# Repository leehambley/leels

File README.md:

# leels: single-axis electronic gearbox

A Rust/Embassy port of the gearbox mode of
[NanoEls H5](https://github.com/kachurovskiy/nanoels), cut down to one job:
the Z lead screw follows the spindle at the selected pitch. There is no WiFi,
no other modes, no X/Y axis, no keyboard or joystick, and no GCode.

```
els-core/   hardware-independent logic, no_std, host-tested (cargo test)
firmware/   esp-hal + esp-rtos (Embassy) binary; ESP32-C6 primary, ESP32-S3 secondary
hil/        hardware-in-the-loop tests: drive a board as the display would
docs/       Nextion page layout
```

## Build and flash

```sh
cd els-core && cargo test          # logic tests on the host

cd firmware
cargo run --release                # ESP32-C6 (default, stable Rust): build, flash, monitor
cargo build --release
cargo run --release --features setup-on-boot   # bench test without a display: hotspot at power-up
cargo +esp s3                      # ESP32-S3: needs the Xtensa toolchain (espup)
```

Board-specific values are in `firmware/src/config.rs`: pinout, motion timing,
display and hotspot settings, and `DEFAULTS`, the machine settings used until
you save your own. Machine settings are normally changed without recompiling,
from the setup page (below).
- **C6** pins (ESP32-C6-DevKitC-1): encoder A 10 / B 11 (Z reserved on 7, not read yet), STEP 18, DIR 19, ENA 20 (S2-SVD servo: wired straight to its opto inputs, see `config.rs`), Nextion TX 22 / RX 23. All are 3.3 V only.
- **C6 breadboard build** (`cargo run --release --features breadboard`), for
  test-driving on a solder breadboard with a 74HCT125 under the DevKit
  driving the servo at 5 V: STEP 18, DIR 8, encoder A 21 / B 15 with
  pull-ups fed from GPIO17 (RX, held high). No ENA: the S2-SVD's enable
  needs 24 V, which this setup doesn't have, so it isn't used (the drive
  enables itself). `config.rs` has the IC wiring. A PCB would use the normal
  pinout.
- **S3** pins: NanoEls H5 pinout (encoder 13/14, STEP 35, DIR 42, ENA 41, Nextion TX 43 / RX 44).

The spindle encoder has open-drain outputs, so the ESP32's internal pull-ups
(already enabled) pull A/B up to 3.3 V. No level shifting is needed on either
chip. For anything beyond slow speeds, fit external pull-ups: see
[Speed limits](#speed-limits-compared-with-nanoels-h5).

Logs go to USB-Serial-JTAG, which leaves both UARTs free.

### Breadboard build: servo wiring (S2-SVD CN2)

| Breadboard | ESP32-C6 side | Wire | CN2 pin |
|---|---|---|---|
| POWER | 5 V rail | brown, green | 3 PP+, 4 PD+ |
| STEP | GPIO18 → 74HCT125 pin 6 (2Y) | blue | 14 PP− |
| DIR | GPIO8 → 74HCT125 pin 8 (3Y) | grey | 5 PD− |

- The drive's inputs are optocouplers (330 Ω + LED): a low on PP− or PD−
  sinks current from the 5 V rail through the LED and back to ground through
  the 74HCT125. STEP pulses low. Nothing here is above 5 V.
- No ENA: this servo's enable input needs 24 V, and this setup has nothing
  above 5 V, so it isn't used. Set **Pn003 = 1** (the drive enables itself
  at power-up) and leave CN2 6, 9 and 10 unconnected.
- The 74HCT125's OE pins (4 and 10) are tied to GND, so STEP and DIR are
  always passed through.
- **Before fitting the DevKit, cut its header pins 1, 2, 3, 9, 10, 12, 13
  and 19.** Their breadboard strips carry the 74HCT125's tie-offs (5 V,
  GND) or its 5 V outputs. 5 V reaches the ESP32 otherwise (GPIO12 is USB
  D−, and one board was lost this way), and a grounded GPIO9 holds the BOOT
  pin low, so the chip starts in download mode and looks dead. USB still
  works without them.

### Bench debugging without a display

```sh
cargo run --release --features bench
```

Logs all Nextion UART traffic (`nextion tx:` / `nextion rx:`) and repeats a
jog sequence (tap right, tap left, 2 s hold right, 2 s hold left) so STEP and
DIR can be scoped. It doesn't start the hotspot: setup mode
locks out jogging (add `setup-on-boot` for that separately).

### Hardware-in-the-loop tests

The `hil` firmware build takes Nextion touch events over the USB port, into
the same buffer the display's UART fills, so the touch parser, UI, motion
task, RMT and STEP pin all run for real. A second PCNT unit counts the pulses
on the STEP pin inside the chip (no wiring) and the count is logged next to
the planned position. The host tests in `hil/` reset the board, tap
components by their HMI object names, and assert on the text and colours the
firmware sends to the display and on the step counts.

```sh
cd firmware && cargo build --release --features hil
espflash flash --chip esp32c6 target/riscv32imac-unknown-none-elf/release/els
cd ../hil && LEELS_PORT=/dev/cu.usbmodem1101 cargo test
```

Without `LEELS_PORT` the tests are skipped. The `hil` build ignores saved
settings and doesn't read the Nextion UART, and the spindle isn't simulated
yet, so threading while engaged isn't covered. Plug the board straight into
the computer: through chains of hubs, flashing and the tests can fail.

## Operation

The screen layout in the Nextion Editor, with each component's object name.
See [docs/nextion.md](docs/nextion.md) for what each one does.

- **Pitch** is a number plus a unit. Type it on the keypad and press **OK**
  (the pending number shows in amber with a cursor; hold **<-** to clear it),
  or tap a preset (**0.01 / 0.05 / 0.1 / 0.5 / 1.0 / 5.0**). **REVERSE** flips direction.
  **UNIT** keeps the number and changes the unit (0.100 mm becomes 0.100").
  Pitch is capped at 1". Pitch can't be changed while engaged: disengage
  first.
- **Engage / Disengage** is one button: it closes the virtual half-nut at the
  current position, or opens it, stopping the lead screw immediately. The
  thread is kept while disengaged: jog back and engage again at the same pitch
  and the button shows `Syncing` until the spindle reaches the thread's phase,
  so the next pass follows the same groove (single-start threads). Changing
  the pitch while disengaged starts a new thread. Jog a little in the cutting
  direction before engaging to take up lead screw backlash.
- **Stops**: pressing Stop L or Stop R sets that stop at the current position.
  The button turns amber and shows the distance still to go to the stop; it turns red with `AT STOP`
  while the carriage rests on it. Pressing it again clears it, but only while
  disengaged or resting on the stop. Stops limit threading and jogging. The
  carriage parks on a stop while the spindle keeps turning. Reverse the
  spindle and it leaves the stop within one turn, still in thread phase. If
  you clear a stop while resting on it, the engage button shows `Syncing` and
  the carriage waits for the thread phase before moving on. **Zero Z** also
  clears both stops.
- **Jog** (disengaged only; refused with a beep while engaged): **Jog L / Jog R**
  move the carriage. Stops limit jogging too.
  - The jog distance (.01 / .1 / 1 / 10 in the current unit, cycled with its
    own button) also sets the jog speed: 0.5 / 2 / 8 / 25 mm/s.
  - A **tap** moves exactly the jog distance at that speed. Repeated taps add
    up.
  - A **hold** longer than 0.4 s runs continuously, starting at the same speed
    and stepping up one speed every second until 25 mm/s. Releasing brakes to
    a stop. Pressing the other direction while moving also brakes.
  - Speeds and timings are set on the setup page.
- **Setup** (only when disengaged and not jogging) turns on a WiFi hotspot,
  `LEELS-SETUP` with password `els-setup`. Both are shown on the display.
  Phones open the settings page automatically as a sign-in page; otherwise
  browse to `http://192.168.4.1/`. The page covers:
  - the encoder (lines, backlash, glitch filter, direction);
  - the lead screw and motor (pitch, steps, start/max speed, acceleration,
    backlash, largest pitch);
  - driver signals (DIR/ENABLE inversion, STEP polarity, pulse width, DIR
    setup time);
  - jog speeds and timings.

  **Backlash** is taken up on every reversal: the motor turns that much
  further, so the Z readout, stops and thread phase stay true. *Measure it*
  opens a wizard for a dial indicator on the carriage: it moves the carriage
  1 mm left, you zero the indicator, it moves 0.5 mm right, and you enter the
  reading. Each further round runs with the value so far switched on and
  refines it, until a round reads 0.5 mm within 0.005 mm. The carriage moves
  from the phone, so keep hands clear. At power-up the controller assumes the
  slack was last taken up moving left.

  **Save** checks the values, writes them to flash and restarts with WiFi off.
  Pressing Setup again leaves without saving. Pins stay fixed in the firmware.

- **Remembered across power-off:** pitch, unit, pitch step and jog distance.
  They're saved 3 s after the last change, once the carriage is idle. Stops
  and position are not saved, because the carriage may be moved while the
  controller is off.

## Saved data

Settings and operator state live in the first four sectors of the flash's NVS
partition, as raw records (not ESP-IDF NVS). Each record has:
- a **magic number**, so blank flash (`0xFF`) and random data are told apart;
- a **format version**, for migrations;
- the **length**, a **sequence number** and a **CRC32**.

Two slots per record are written alternately, and the newer valid one wins,
so a power cut during a save keeps the previous copy. Blank flash means
first boot, and the defaults are used. A damaged record, or one from a newer
firmware, also falls back to the defaults, and the display says so. Flash
writes pause the CPU for tens of milliseconds, so they only happen while
nothing moves.

## How motion works

Software plans the motion and hardware times the pulses: the same split as
LinuxCNC's stepgen or Klipper.

```
 PCNT spindle count ─► predict spindle position at end of next segment
                         │
       commands ───────► gearbox (engaged) or jog (disengaged) ─► target
                         │
                       StepGen: velocity/acceleration-limited plan for one
                       250 µs segment → exact STEP pulse times
                         │
                       RMT plays the segment in hardware (100 ns resolution)
                       while the next segment is planned
```

- `motion_task` runs on a high-priority interrupt executor, paced by the RMT
  peripheral. Each loop starts playing the segment planned last time, plans
  the next one, then waits for playback to finish. That's 4,000 wakeups a second.
- The gearbox target is `p_ref + (spindle − s_ref) · pitch·steps / (screw·counts)`,
  in exact integer maths, including the fraction of a step. It's evaluated at
  the spindle position predicted for the end of the segment, so the carriage
  doesn't lag the spindle.
- StepGen (`els-core/src/stepgen.rs`) sets each segment's velocity from:
  - feed-forward: how fast the target is moving;
  - a correction for any remaining error, limited so the error could still be
    braked away (`√(2·a·error)`).

  Velocity is constant within a segment, so pulses are evenly spaced. Host tests
  check a steady spindle gives step intervals within ±0.1 µs of ideal, and that
  a realistic spindle run-up never lags by more than 1 step.
- The maximum step rate is set by the pulse width and the driver (30 k steps/s
  configured), not by a software tick.
- The UI and display run on the normal thread executor. They talk to motion
  through a command channel and a status snapshot.

Known limitation: esp-hal's RMT driver restarts transmission for each
segment, which leaves a few-µs gap between segments. Position isn't affected,
because every step is still planned against the spindle. A gapless version
would need a custom RMT ring-buffer driver.

## Speed limits compared with NanoEls H5

Example machine: a 1200-line encoder driven 1:1 by the spindle (2400 counts
per revolution), 800 steps per screw turn, 4 mm screw (200 steps/mm).
Channel A then runs at **20 Hz per spindle rpm**, and at 1 mm pitch the motor
needs **3.33 steps/s per rpm**.

| | NanoEls H5 original (S3, Arduino) | leels on C6 (primary) | leels on S3 |
|---|---|---|---|
| CPU | 2 × 240 MHz; motion busy-loops on core 1 | 1 × 160 MHz, shared | 2 × 240 MHz; everything on core 0 |
| Encoder counting | PCNT hardware | PCNT hardware | PCNT hardware |
| Encoder glitch filter | 12.5 ns | 0.5 µs (settable) | 0.5 µs (settable) |
| STEP pulses made by | software in `loop()`, polling `micros()` | RMT hardware, 100 ns resolution | RMT hardware, 100 ns resolution |
| Step timing jitter | about one `loop()` pass plus 1 µs `micros()` steps; interrupts on core 1 add to it (estimated) | 0.1 µs within a segment; ~11 µs pause every 250 µs (measured) | same design; pause likely shorter (not measured) |
| Pulse width | length of the code between the two pin writes | exactly as set (2.5 µs default) | exactly as set |
| Step-rate ceiling from the controller | speed of `loop()`: tens of kHz, estimated | 30k steps/s as configured; ~128k possible (32 steps per segment) | same as C6 |
| CPU used by motion | all of core 1 | ~75 µs per 250 µs segment, ~30% (measured) | expected ~20% of core 0 at 240 MHz (not measured) |
| Lag behind the spindle | about one loop pass | ≤ 1 step during spin-up (host tests; position predicted ahead) | same as C6 |

**Maximum rpm is the same on all three.** With hardware pull-ups none of the
controllers is the limit. What is:

1. **The encoder's rated output frequency.** Cheap optical encoders are often
   rated around 100 kHz; check your datasheet. 100 kHz / 20 Hz per rpm =
   **5,000 rpm**. The PCNT counter itself handles MHz rates, and leels'
   0.5 µs glitch filter still passes up to about 1 MHz (50,000 rpm).
2. **The stepper at speed.** A typical stepper at 4× microstepping becomes
   unreliable around 10–15k steps/s (depends on supply voltage and load).
   That's about **3,000–4,500 rpm at 1 mm pitch** and **120–180 rpm at 1"**
   (85 steps/s per rpm). The same motor limits all three controllers.
3. **leels' `speed_max`** (30k steps/s by default) is about 9,000 rpm at
   1 mm pitch, so it's well clear of both.

### Pull-ups and encoder edges

An open-drain output only pulls low. The pull-up resistor and the capacitance
of the cable and input (roughly 100 pF per metre of cable) set how slowly each
edge rises. An input reads high at about 75% of 3.3 V, which takes about
1.4 × R × C.

| Pull-up to 3.3 V | Rise time (1 m cable, ~100 pF) | Rise time (3 m, ~300 pF) | rpm before edges get marginal* |
|---|---|---|---|
| internal, ~45 kΩ | ~6 µs | ~19 µs | ~4,000 (1 m), ~1,300 (3 m) |
| external 4.7 kΩ | ~0.7 µs | ~2 µs | encoder-limited (~5,000) |
| external 2.2 kΩ | ~0.3 µs | ~1 µs | encoder-limited (~5,000) |

\*Rise time equal to half a period of channel A: 1 / (2 × 20 Hz × rpm).
Before that point, slow edges can also count twice if noise crosses the
threshold. This applies equally to the original firmware, which used the
same internal pull-ups.

Use **2.2–4.7 kΩ to 3.3 V, not 5 V**: ESP32 inputs aren't 5 V tolerant, and
at 3.3 V the encoder only has to sink about 1.5 mA.

### Multiple cores

- **C6:** one main core; its second core is a 20 MHz low-power core that can't
  run any of this. Motion runs on a high-priority interrupt executor that
  preempts the display, touch and WiFi tasks, and uses ~30% of the core.
- **S3:** motion *can* be moved to core 1 (`esp_rtos::start_second_core`,
  then start the motion interrupt executor there). It **isn't needed for
  speed**: RMT times the pulses, and planning only has to finish within each
  250 µs segment, which it does with room to spare even on the C6. The only
  benefit would be isolating motion from WiFi interrupts on the S3. Flash
  writes stall both cores regardless, which is why saves only happen while
  idle. Worth doing only if an S3 build ever shows planning overruns.

## Not carried over

Saving stops and position across power-off, backlash compensation, TPI
entry, the max-travel E-stop, and enable/disable per axis.

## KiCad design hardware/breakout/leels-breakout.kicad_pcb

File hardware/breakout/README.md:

# Breakout board

A carrier for the ESP32-C6-DevKitC-1: the DevKit plugs into two 1x16 female
sockets (rows 22.86 mm apart) and sits about 8.5 mm above this board. All parts
are through-hole. The buffer IC, transistor, resistors and capacitors sit under
the DevKit, so keep them low: no IC socket, resistors flat.

- Left edge: encoder terminal (bottom to top: 5V, GND, A, B, Z) and shield
  GND terminal.
- Right edge: Nextion (JST-XH 4), servo terminal (5V, STEP, DIR, ENA, GND) and
  5 V in.
- The board stops where the DevKit's PCB stops, so nothing is under its
  antenna.

Firmware: the normal C6 build (`cargo run --release`), not `--features breadboard`.

## Regenerating the PCB

The schematic is the source. The board is rebuilt from it by script, then
routed with [Freerouting](https://github.com/freerouting/freerouting) 1.9.0:

```sh
KP=/Applications/KiCad/KiCad.app/Contents/Frameworks/Python.framework/Versions/3.9/bin/python3
kicad-cli sch export netlist --format kicadxml -o net.xml leels-breakout.kicad_sch
$KP build_pcb.py net.xml         # outline, placement, GND pours, stitching vias
$KP route.py export board.dsn
java -jar freerouting-1.9.0.jar -de board.dsn -do board.ses -mp 100 -inc Ground
$KP route.py import board.ses    # also refills the pours
kicad-cli pcb drc --schematic-parity --refill-zones leels-breakout.kicad_pcb
```

Placement lives in `build_pcb.py` (`PLACE`). GND is not routed; the pours on
both layers and the stitching vias carry it. Net classes (0.3 mm signals,
0.6 mm power and ground) are in `leels-breakout.kicad_pro`.

`leels.pretty/ESP32-C6-DevKitC-1_Sockets` is Espressif's DevKitC-1 footprint
with its courtyard limited to the socket rows, so parts may sit under the
DevKit.

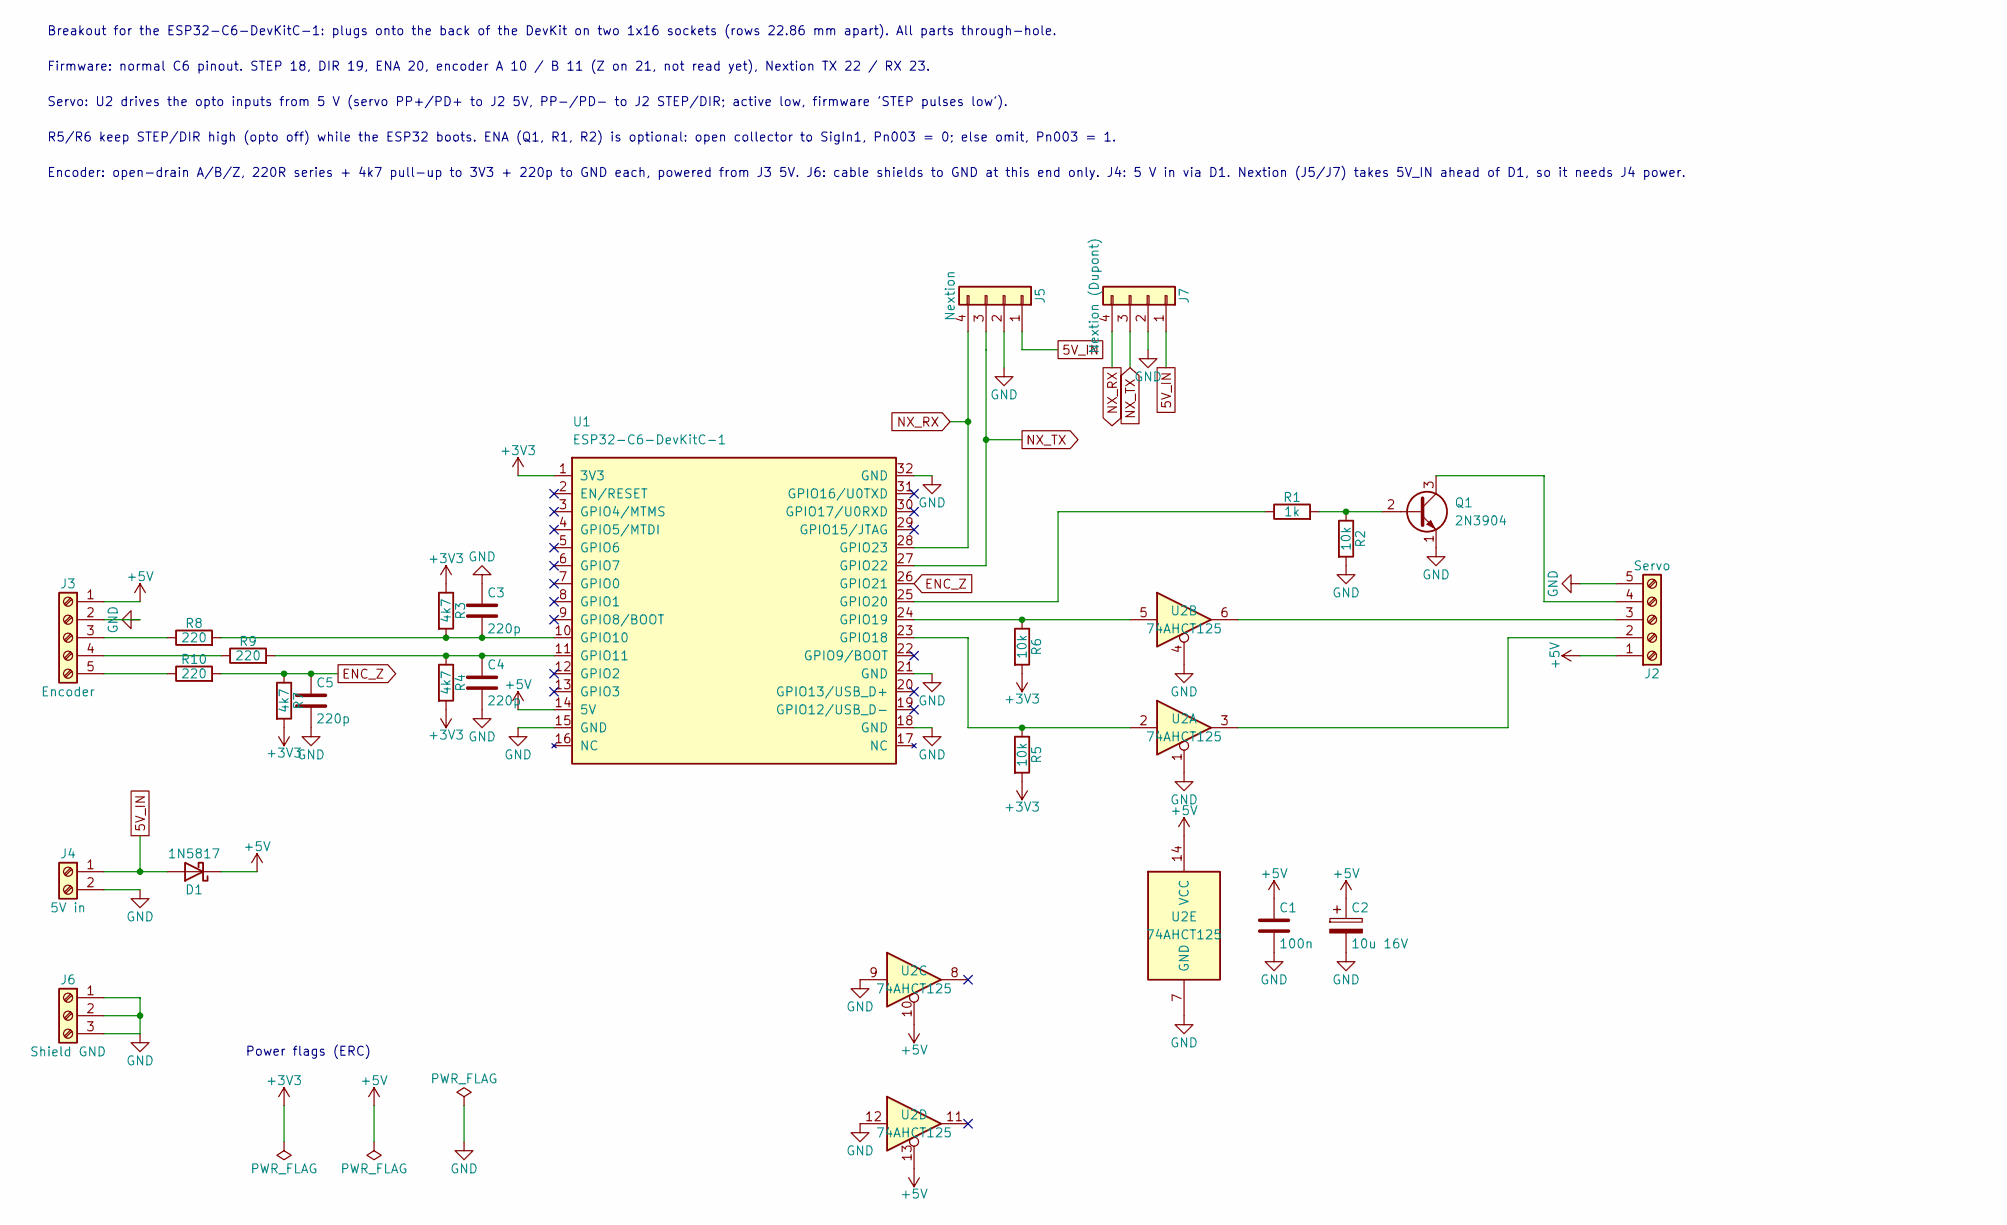
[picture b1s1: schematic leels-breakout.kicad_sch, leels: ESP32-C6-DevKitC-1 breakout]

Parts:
C1: 100n; C_Axial_L3.8mm_D2.6mm_P7.50mm_Horizontal
C2: 10u 16V; CP_Radial_D5.0mm_P2.00mm
C3, C4, C5: 220p; C_Axial_L3.8mm_D2.6mm_P7.50mm_Horizontal
D1: 1N5817; D_DO-41_SOD81_P10.16mm_Horizontal
J2: Servo; TerminalBlock_Phoenix_MKDS-1,5-5-5.08_1x05_P5.08mm_Horizont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
J3: Encoder; TerminalBlock_Phoenix_MKDS-1,5-5-5.08_1x05_P5.08mm_Horizont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
J4: 5V in; TerminalBlock_Phoenix_MKDS-1,5-2-5.08_1x02_P5.08mm_Horizont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
J5: Nextion; JST_XH_B4B-XH-A_1x04_P2.50mm_Vertical
J6: Shield GND; TerminalBlock_Phoenix_MKDS-1,5-3-5.08_1x03_P5.08mm_Horizont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
J7: Nextion (Dupont); PinHeader_1x04_P2.54mm_Vertical
Q1: 2N3904; TO-92_W4.0mm_StaggerEven_Horizontal_FlatSideDown
R1: 1k; R_Axial_DIN0207_L6.3mm_D2.5mm_P7.62mm_Horizontal
R2, R5, R6: 10k; R_Axial_DIN0207_L6.3mm_D2.5mm_P7.62mm_Horizontal
R3, R4, R7: 4k7; R_Axial_DIN0207_L6.3mm_D2.5mm_P7.62mm_Horizontal
R8, R9, R10: 220; R_Axial_DIN0207_L6.3mm_D2.5mm_P7.62mm_Horizontal
U1: ESP32-C6-DevKitC-1; ESP32-C6-DevKitC-1_Sockets
U2: 74AHCT125; DIP-14_W7.62mm

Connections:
5V_IN: D1.2 (A), J4.1, J5.1, J7.1
+3V3: R3.1, R4.2, R5.2, R6.2, R7.2, U1.1 (3V3)
+5V: C1.1, C2.1, D1.1 (K), J2.1, J3.1, U1.14 (5V), U2.10, U2.13, U2.14 (VCC)
ENC_Z: C5.1, R7.1, R10.2, U1.26 (GPIO21)
GND: C1.2, C2.2, C3.1, C4.2, C5.2, J2.5, J3.2, J4.2, J5.2, J6.1, J6.2, J6.3, J7.2, Q1.1 (E), R2.2, U1.15 (GND), U1.18 (GND), U1.21 (GND), U1.32 (GND), U2.1, U2.4, U2.7 (GND), U2.9, U2.12
NX_RX: J5.4, J7.4, U1.28 (GPIO23)
NX_TX: J5.3, J7.3, U1.27 (GPIO22)
unnamed: J2.2, U2.3
unnamed: J2.3, U2.6
unnamed: J2.4, Q1.3 (C)
unnamed: J3.3, R8.1
unnamed: J3.4, R9.1
unnamed: J3.5, R10.1
unnamed: Q1.2 (B), R1.2, R2.1
unnamed: C3.2, R3.2, R8.2, U1.10 (GPIO10)
unnamed: C4.1, R4.1, R9.2, U1.11 (GPIO11)
unnamed: R5.1, U1.23 (GPIO18), U2.2
unnamed: R6.1, U1.24 (GPIO19), U2.5
unnamed: R1.1, U1.25 (GPIO20)

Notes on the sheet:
Breakout for the ESP32-C6-DevKitC-1: plugs onto the back of the DevKit on two 1x16 sockets (rows 22.86 mm apart). All parts through-hole.
Firmware: normal C6 pinout. STEP 18, DIR 19, ENA 20, encoder A 10 / B 11 (Z on 21, not read yet), Nextion TX 22 / RX 23.
Servo: U2 drives the opto inputs from 5 V (servo PP+/PD+ to J2 5V, PP-/PD- to J2 STEP/DIR; active low, firmware 'STEP pulses low').
R5/R6 keep STEP/DIR high (opto off) while the ESP32 boots. ENA (Q1, R1, R2) is optional: open collector to SigIn1, Pn003 = 0; else omit, Pn003 = 1.
Encoder: open-drain A/B/Z, 220R series + 4k7 pull-up to 3V3 + 220p to GND each, powered from J3 5V. J6: cable shields to GND at this end only. J4: 5 V in via D1. Nextion (J5/J7) takes 5V_IN ahead of D1, so it needs J4 power.
Power flags (ERC)

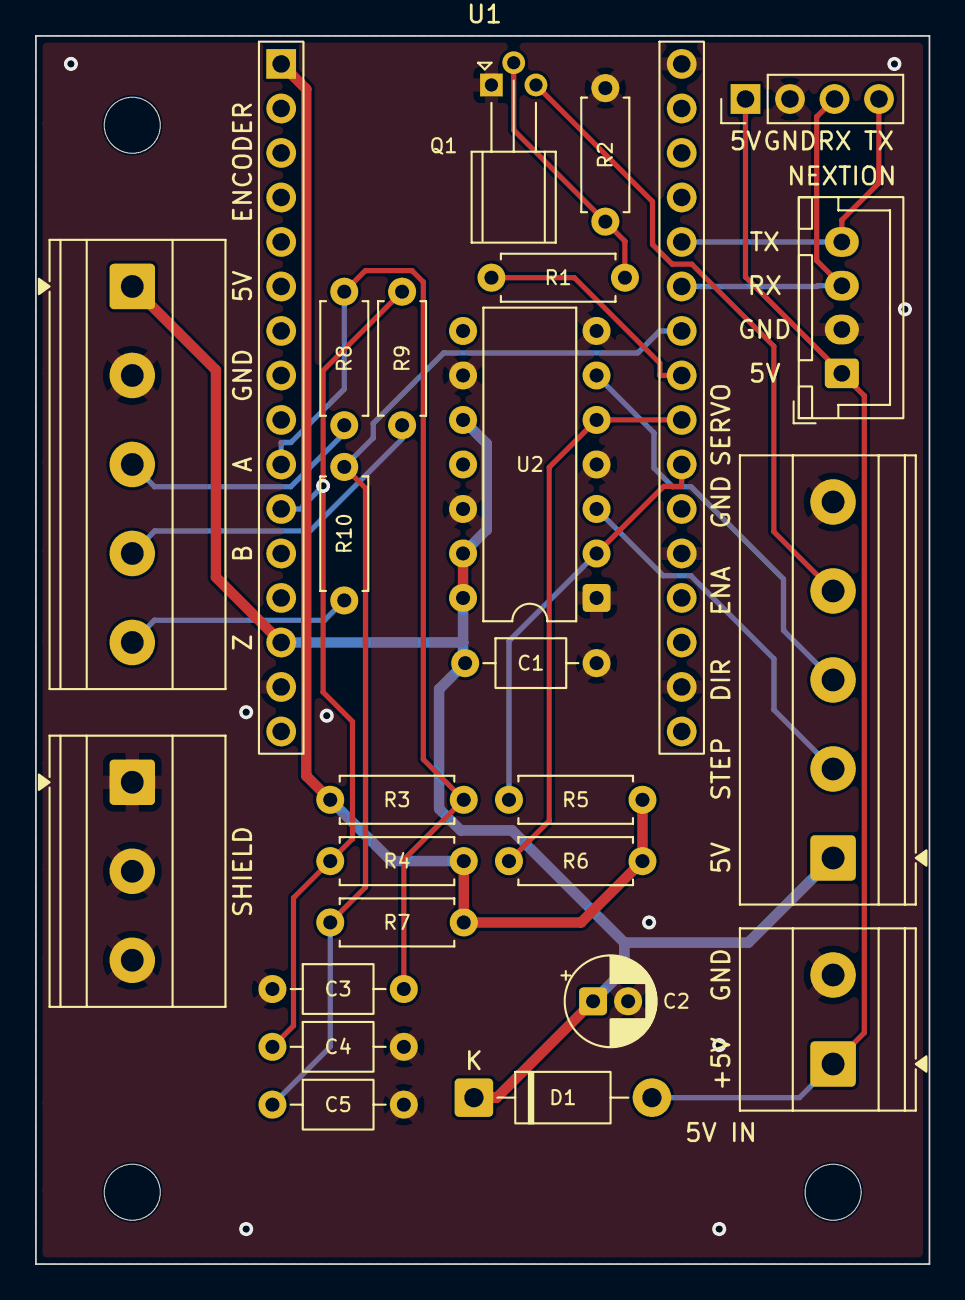
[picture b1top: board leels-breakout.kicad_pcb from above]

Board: 2 copper layers, 51.0 x 70.1 mm, 28 parts (0 on the bottom side), 19 nets.

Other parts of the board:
H1, H2, H3: MountingHole_3.2mm_M3
